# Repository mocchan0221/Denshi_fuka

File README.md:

# プログラマブルデジタル電子負荷
## What's this?
PCから制御、データの受信などが出来、電流値を好きな関数などで制御できる電子負荷です。

高電圧・小電流回路と低電圧・大電流回路の2つを使い分けることが出来ます。

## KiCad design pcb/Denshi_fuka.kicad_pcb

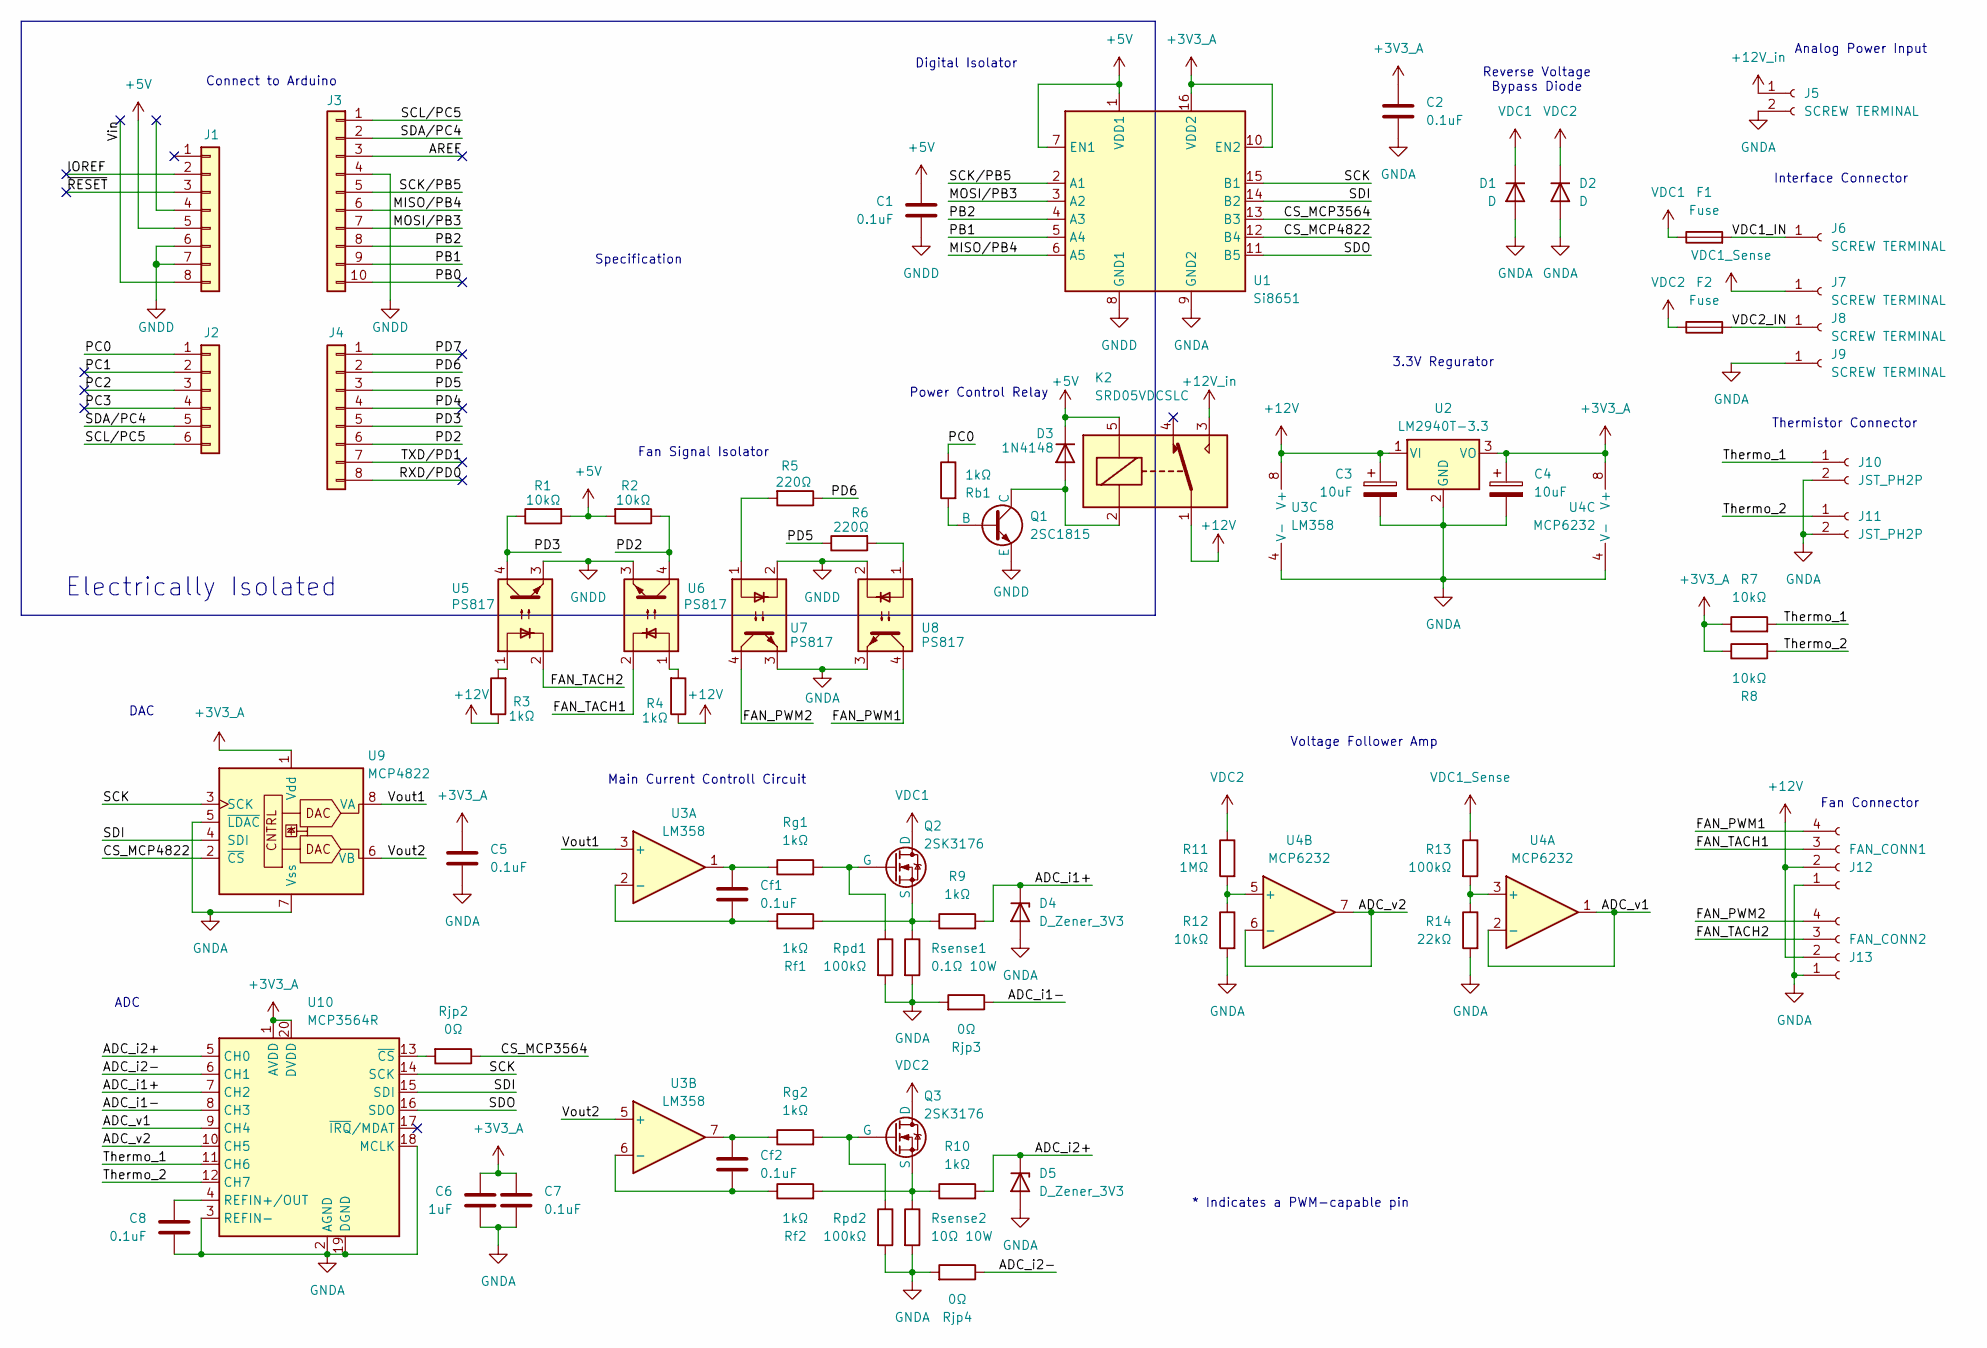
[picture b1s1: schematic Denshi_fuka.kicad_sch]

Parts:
C1, C2, C5, C7, C8: 0.1uF; C_Disc_D5.0mm_W2.5mm_P5.00mm
C3, C4: 10uF; CP_Radial_D5.0mm_P2.00mm
C6: 1uF; C_Disc_D3.0mm_W1.6mm_P2.50mm
Cf1, Cf2: 0.1uF; C_Disc_D5.0mm_W2.5mm_P5.00mm
D1, D2: D; TO-220-2_Vertical
D3: 1N4148; D_DO-35_SOD27_P7.62mm_Horizontal
D4, D5: D_Zener_3V3; D_DO-35_SOD27_P7.62mm_Horizontal
F1, F2: Fuse; MF-563
J1, J4: Conn_01x08; PinHeader_1x08_P2.54mm_Vertical
J2: Conn_01x06; PinHeader_1x06_P2.54mm_Vertical
J3: Conn_01x10; PinHeader_1x10_P2.54mm_Vertical
J5: SCREW TERMINAL; TerminalBlock_Phoenix_PT-1,5-2-5.0-H_1x02_P5.00mm_Horizontal
J6, J7, J8, J9: SCREW TERMINAL; PCB-20
J10, J11: JST_PH2P; JST_PH_B2B-PH-K_1x02_P2.00mm_Vertical
J12: FAN_CONN1; FanPinHeader_1x04_P2.54mm_Vertical
J13: FAN_CONN2; FanPinHeader_1x04_P2.54mm_Vertical
K2: SRD05VDCSLC; Relay_SPDT_SANYOU_SRD_Series_Form_C
Q1: 2SC1815; TO-92_Inline
Q2, Q3: 2SK3176; TO-247-3_Horizontal_TabUp
R1, R2, R7, R8, R12: 10kΩ; R_Axial_DIN0207_L6.3mm_D2.5mm_P10.16mm_Horizontal
R3, R4, R9, R10: 1kΩ; R_Axial_DIN0207_L6.3mm_D2.5mm_P10.16mm_Horizontal
R5, R6: 220Ω; R_Axial_DIN0207_L6.3mm_D2.5mm_P10.16mm_Horizontal
R11: 1MΩ; R_Axial_DIN0207_L6.3mm_D2.5mm_P10.16mm_Horizontal
R13: 100kΩ; R_Axial_DIN0207_L6.3mm_D2.5mm_P10.16mm_Horizontal
R14: 22kΩ; R_Axial_DIN0207_L6.3mm_D2.5mm_P10.16mm_Horizontal
Rb1: 1kΩ; R_Axial_DIN0207_L6.3mm_D2.5mm_P10.16mm_Horizontal
Rf1, Rf2: 1kΩ; R_Axial_DIN0309_L9.0mm_D3.2mm_P12.70mm_Horizontal
Rg1, Rg2: 1kΩ; R_Axial_DIN0309_L9.0mm_D3.2mm_P12.70mm_Horizontal
Rjp2: 0Ω; R_Axial_DIN0309_L9.0mm_D3.2mm_P15.24mm_Horizontal
Rjp3, Rjp4: 0Ω; R_Axial_DIN0207_L6.3mm_D2.5mm_P2.54mm_Vertical
Rpd1, Rpd2: 100kΩ; R_Axial_DIN0207_L6.3mm_D2.5mm_P15.24mm_Horizontal
Rsense1: 0.1Ω 10W; R_Axial_Power_L48.0mm_W12.5mm_P55.88mm
Rsense2: 10Ω 10W; R_Axial_Power_L48.0mm_W12.5mm_P55.88mm
U1: Si8651; DIP-16_W15.24mm (600mil)
U2: LM2940T-3.3; TO-220-3_Vertical
U3: LM358; DIP-8_W7.62mm_Socket
U4: MCP6232; DIP-8_W7.62mm_Socket_LongPads
U5, U6, U7, U8: PS817; DIP-4_W7.62mm_LongPads
U9: MCP4822; DIP-8_W7.62mm_Socket_LongPads
U10: MCP3564R; DIP-20_W15.24mm_Socket_LongPads

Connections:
+3V3_A: C2.1, C4.1, C5.1, C6.1, C7.1, R7.1, R8.1, U1.10 (EN2), U1.16 (VDD2), U2.3 (VO), U4.8 (V+), U9.1 (Vdd), U10.1 (AVDD), U10.20 (DVDD)
+5V: C1.1, D3.1 (K), J1.5, K2.5, R1.2, R2.2, U1.1 (VDD1), U1.7 (EN1)
+12V: C3.1, J12.2, J13.2, K2.1, R3.1, R4.1, U2.1 (VI), U3.8 (V+)
+12V_in: J5.1, K2.3
/ADC_i1+: D4.1 (K), R9.2, U10.7 (CH2)
/ADC_i1-: Rjp3.1, U10.8 (CH3)
/ADC_i2+: D5.1 (K), R10.2, U10.5 (CH0)
/ADC_i2-: Rjp4.1, U10.6 (CH1)
/ADC_v1: U4.1, U4.2 (-), U10.9 (CH4)
/ADC_v2: U4.6 (-), U4.7, U10.10 (CH5)
/AREF: J3.3
/CS_MCP3564: Rjp2.1, U1.13 (B3)
/CS_MCP4822: U1.12 (B4), U9.2 (~CS)
/FAN_PWM1: J12.4, U8.4
/FAN_PWM2: J13.4, U7.4
/FAN_TACH1: J12.3, U6.2
/FAN_TACH2: J13.3, U5.2
/IOREF: J1.2
/MISO/PB4: J3.6, U1.6 (A5)
/MOSI/PB3: J3.7, U1.3 (A2)
/PB0: J3.10
/PB1: J3.9, U1.5 (A4)
/PB2: J3.8, U1.4 (A3)
/PC0: J2.1, Rb1.1
/PC1: J2.2
/PC2: J2.3
/PC3: J2.4
/PD2: J4.6, R2.1, U6.4
/PD3: J4.5, R1.1, U5.4
/PD4: J4.4
/PD5: J4.3, R6.1
/PD6: J4.2, R5.1
/PD7: J4.1
/RXD/PD0: J4.8
/SCK: U1.15 (B1), U9.3 (SCK), U10.14 (SCK)
/SCK/PB5: J3.5, U1.2 (A1)
/SCL/PC5: J2.6, J3.1
/SDA/PC4: J2.5, J3.2
/SDI: U1.14 (B2), U9.4 (SDI), U10.15 (SDI)
/SDO: U1.11 (B5), U10.16 (SDO)
/TXD/PD1: J4.7
/Thermo_1: J10.1, R7.2, U10.11 (CH6)
/Thermo_2: J11.1, R8.2, U10.12 (CH7)
/VDC1_IN: F1.2, J6.1 (Pin_1_1)
/VDC2_IN: F2.2, J8.1 (Pin_1_1)
/Vin: J1.8
/Vout1: U3.3 (+), U9.8 (VA)
/Vout2: U3.5 (+), U9.6 (VB)
/~RESET: J1.3
GNDA: C2.2, C3.2, C4.2, C5.2, C6.2, C7.2, C8.2, D1.2 (A), D2.2 (A), D4.2 (A), D5.2 (A), J5.2, J9.1 (Pin_1_1), J10.2, J11.2, J12.1, J13.1, R12.2, R14.2, Rjp3.2, Rjp4.2, Rpd1.2, Rpd2.2, Rsense1.2, Rsense2.2, U1.9 (GND2), U2.2 (GND), U3.4 (V-), U4.4 (V-), U7.3, U8.3, U9.5 (~LDAC), U9.7 (Vss), U10.2 (AGND), U10.3 (REFIN-), U10.18 (MCLK), U10.19 (DGND)
GNDD: C1.2, J1.6, J1.7, J3.4, Q1.3 (E), U1.8 (GND1), U5.3, U6.3, U7.2, U8.2
unnamed: Cf1.1, Rg1.1, U3.1
unnamed: Cf2.1, Rg2.1, U3.7
unnamed: D3.2 (A), K2.2, Q1.1 (C)
unnamed: Q1.2 (B), Rb1.2
unnamed: Q2.1 (G), Rg1.2, Rpd1.1
unnamed: Q2.3 (S), R9.1, Rf1.2, Rsense1.1
unnamed: Q3.1 (G), Rg2.2, Rpd2.1
unnamed: Q3.3 (S), R10.1, Rf2.2, Rsense2.1
unnamed: R3.2, U5.1
unnamed: R4.2, U6.1
unnamed: R5.2, U7.1
unnamed: R6.2, U8.1
unnamed: Cf1.2, Rf1.1, U3.2 (-)
unnamed: Cf2.2, Rf2.1, U3.6 (-)
unnamed: R13.2, R14.1, U4.3 (+)
unnamed: R11.2, R12.1, U4.5 (+)
unnamed: C8.1, U10.4 (REFIN+/OUT)
unnamed: Rjp2.2, U10.13 (~CS)
VDC1: D1.1 (K), F1.1, Q2.2 (D)
VDC1_Sense: J7.1 (Pin_1_1), R13.1
VDC2: D2.1 (K), F2.1, Q3.2 (D), R11.1

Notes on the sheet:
Interface Connector
Electrically Isolated
Fan Connector
Analog Power Input
Digital Isolator
Specification
Fan Signal Isolator
Thermistor Connector
Main Current Controll Circuit
Voltage Follower Amp
Power Control Relay
* Indicates a PWM-capable pin
3.3V Regurator
Reverse Voltage Bypass Diode
Connect to Arduino
ADC
DAC

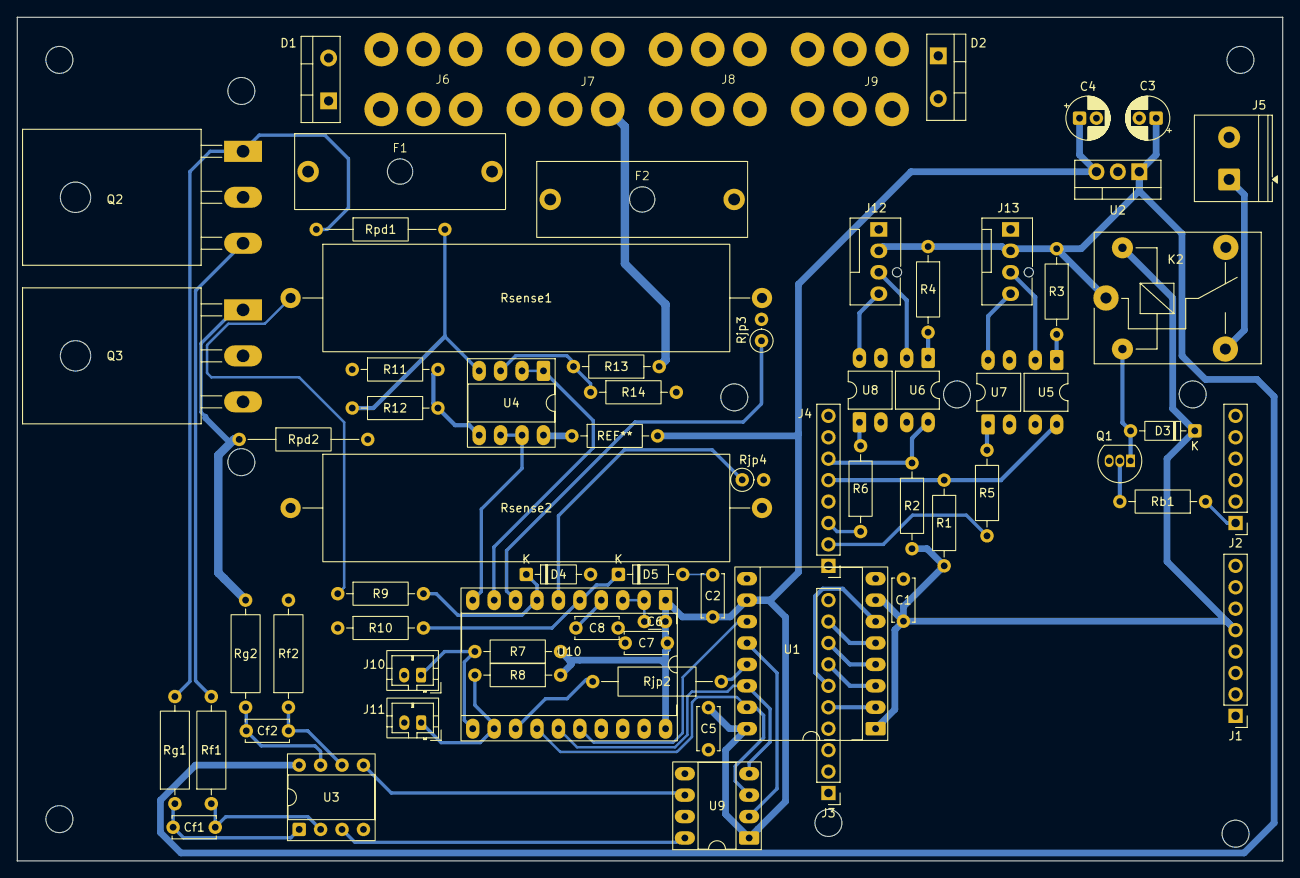
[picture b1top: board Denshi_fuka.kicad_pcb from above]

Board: 2 copper layers, 150.0 x 100.0 mm, 74 parts (0 on the bottom side), 60 nets.

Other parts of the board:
MH1, MH2, MH3, MH4: MountingHole_3.2mm

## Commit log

2026-04-24 add pio project and modify circuit
2026-04-24 add PC and BOM
2026-04-28 schematic completed!
2026-04-29 modify sch
2026-04-30 little modify
2026-05-01 add some circuit
2026-05-08 Fuck
2026-05-08 test plot
2026-05-09 test step
2026-05-10 pcb kansei
2026-05-11 pcb first done
2026-05-11 firmware sintyoku ari
2026-05-12 firmware done!
2026-05-12 soft made
2026-05-13 modify
2026-05-15 aruteido done
2026-05-17 add daiza
2026-05-17 modify daiza
2026-05-17 add macro function
